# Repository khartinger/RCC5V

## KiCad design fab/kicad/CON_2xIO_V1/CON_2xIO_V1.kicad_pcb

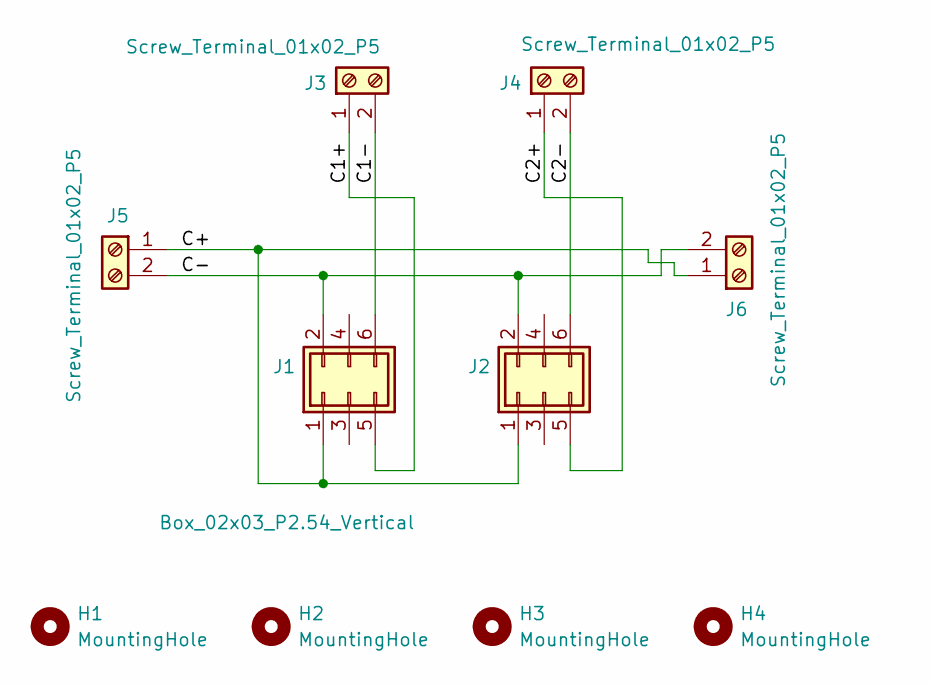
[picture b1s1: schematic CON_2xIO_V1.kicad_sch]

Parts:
H1, H2, H3, H4: MountingHole; MountingHole_2.2mm_M2_Pad_TopBottom_kh
J1: Box_02x03_P2.54_Vertical; Box_02x03_P2.54mm_Vertical_kh
J2: Box_02x03_P2.54mm_Vertical_kh
J3, J4, J5, J6: Screw_Terminal_01x02_P5

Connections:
/C1+: J1.5, J3.1
/C1-: J1.6, J3.2
/C2+: J2.5, J4.1
/C2-: J2.6, J4.2
/C+: J1.1, J2.1, J5.1, J6.1
/C-: J1.2, J2.2, J5.2, J6.2

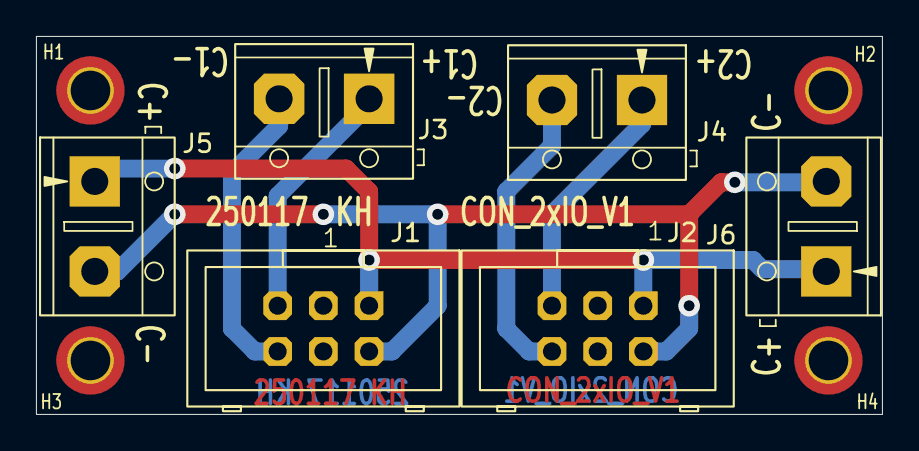
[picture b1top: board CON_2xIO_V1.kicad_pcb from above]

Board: 2 copper layers, 47.0 x 21.0 mm, 10 parts (0 on the bottom side), 6 nets.

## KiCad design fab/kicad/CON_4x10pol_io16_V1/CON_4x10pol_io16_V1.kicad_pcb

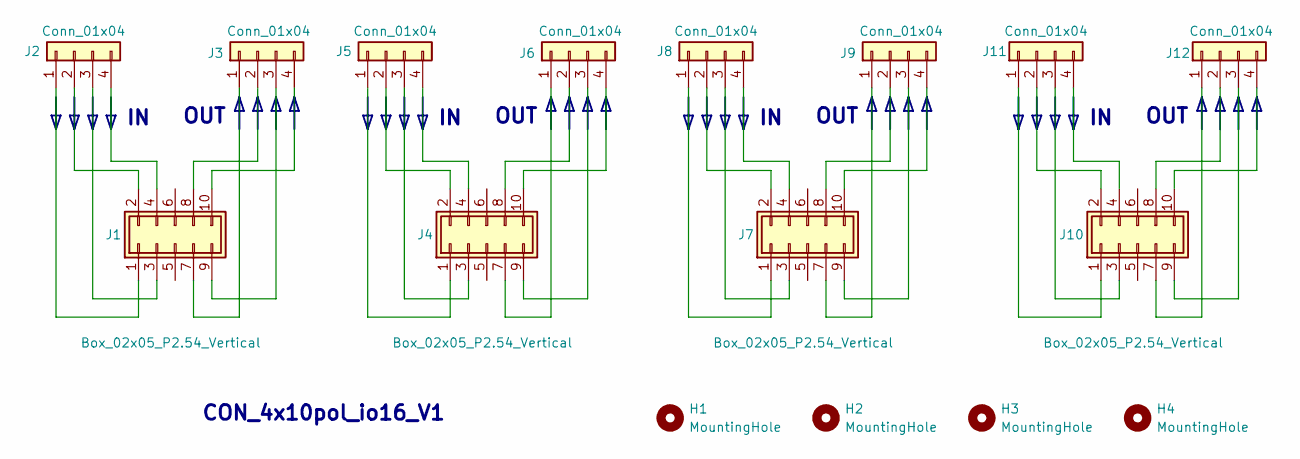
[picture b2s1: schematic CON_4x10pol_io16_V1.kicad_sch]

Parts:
H1, H2, H3, H4: MountingHole; MountingHole_2.2mm_M2_Pad_TopBottom_kh
J1, J4, J7, J10: Box_02x05_P2.54_Vertical; Box_02x05_P2.54mm_Vertical_kh
J2, J3, J5, J6, J8, J9, J11, J12: Conn_01x04; PinSocket_1x04_P2.54mm_8_Vertical_kh

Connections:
unnamed: J1.1, J2.1
unnamed: J1.2, J2.2
unnamed: J1.3, J2.3
unnamed: J1.4, J2.4
unnamed: J1.7, J3.1
unnamed: J1.8, J3.2
unnamed: J1.9, J3.3
unnamed: J1.10, J3.4
unnamed: J4.1, J5.1
unnamed: J4.2, J5.2
unnamed: J4.3, J5.3
unnamed: J4.4, J5.4
unnamed: J4.7, J6.1
unnamed: J4.8, J6.2
unnamed: J4.9, J6.3
unnamed: J4.10, J6.4
unnamed: J7.1, J8.1
unnamed: J7.2, J8.2
unnamed: J7.3, J8.3
unnamed: J7.4, J8.4
unnamed: J7.7, J9.1
unnamed: J7.8, J9.2
unnamed: J7.9, J9.3
unnamed: J7.10, J9.4
unnamed: J10.1, J11.1
unnamed: J10.2, J11.2
unnamed: J10.3, J11.3
unnamed: J10.4, J11.4
unnamed: J10.7, J12.1
unnamed: J10.8, J12.2
unnamed: J10.9, J12.3
unnamed: J10.10, J12.4

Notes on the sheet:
OUT
CON_4x10pol_io16_V1

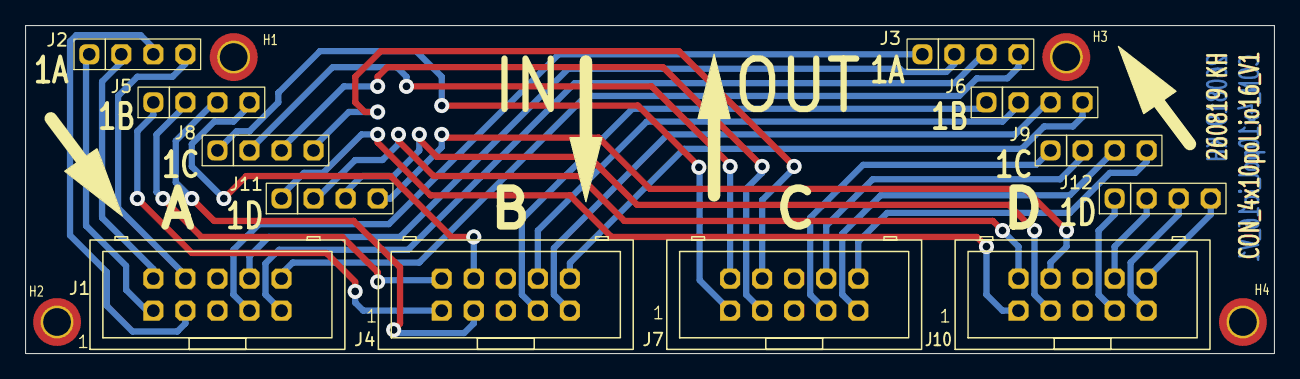
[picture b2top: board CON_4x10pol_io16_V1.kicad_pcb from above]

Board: 2 copper layers, 99.0 x 26.0 mm, 16 parts (0 on the bottom side), 32 nets.

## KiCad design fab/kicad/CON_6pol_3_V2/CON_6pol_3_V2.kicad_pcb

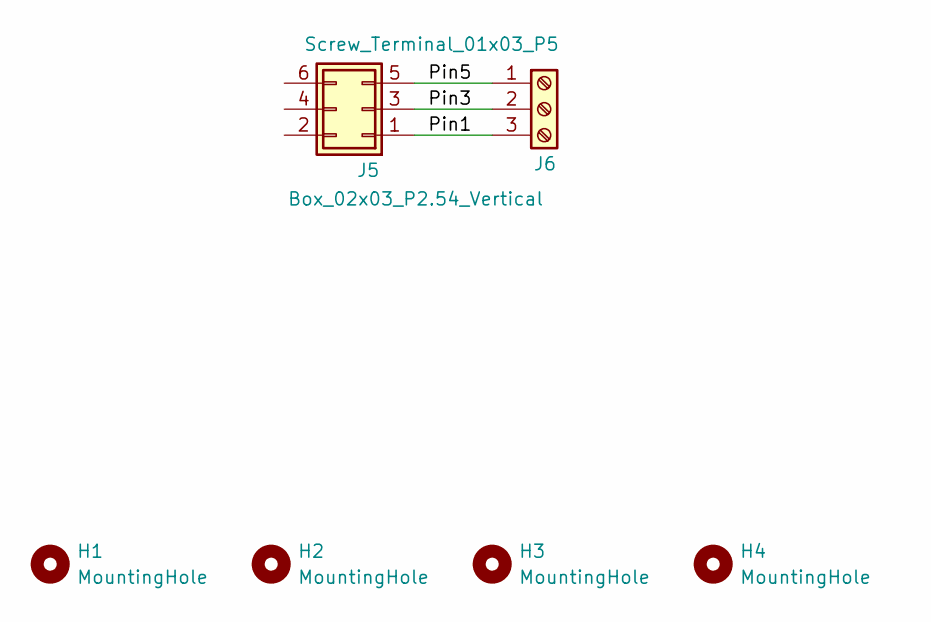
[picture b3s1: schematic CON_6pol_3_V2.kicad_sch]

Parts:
H1, H2, H3, H4: MountingHole; MountingHole_2.2mm_M2_Pad_TopBottom_kh
J5: Box_02x03_P2.54_Vertical; Box_02x03_P2.54mm_Vertical_kh
J6: Screw_Terminal_01x03_P5

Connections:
/Pin1: J5.1, J6.3
/Pin3: J5.3, J6.2
/Pin5: J5.5, J6.1

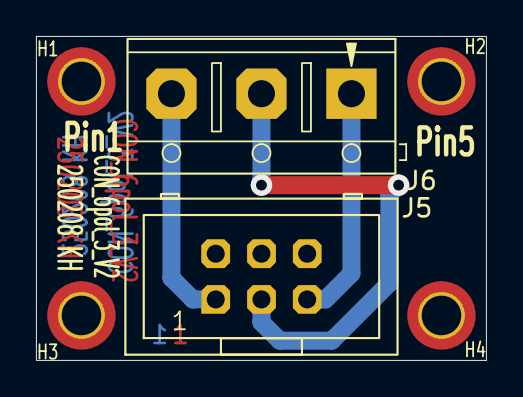
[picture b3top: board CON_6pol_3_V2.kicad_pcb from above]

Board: 2 copper layers, 25.0 x 18.0 mm, 6 parts (0 on the bottom side), 3 nets.

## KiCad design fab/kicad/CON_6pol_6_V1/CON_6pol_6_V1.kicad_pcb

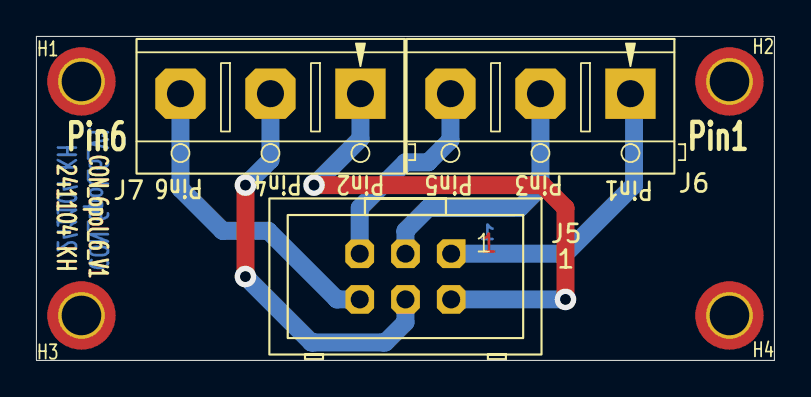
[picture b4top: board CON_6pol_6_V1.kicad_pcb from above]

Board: 2 copper layers, 41.0 x 18.0 mm, 7 parts (0 on the bottom side), 6 nets.

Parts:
H1, H2, H3, H4: MountingHole; MountingHole_2.2mm_M2_Pad_TopBottom_kh
J5: Box_02x03_P2.54_Vertical; Box_02x03_P2.54mm_Vertical_kh
J6, J7: Screw_Terminal_01x03_P5

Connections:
/Pin1: J5.1, J6.1
/Pin2: J5.2, J7.1
/Pin3: J5.3, J6.2
/Pin4: J5.4, J7.2
/Pin5: J5.5, J6.3
/Pin6: J5.6, J7.3

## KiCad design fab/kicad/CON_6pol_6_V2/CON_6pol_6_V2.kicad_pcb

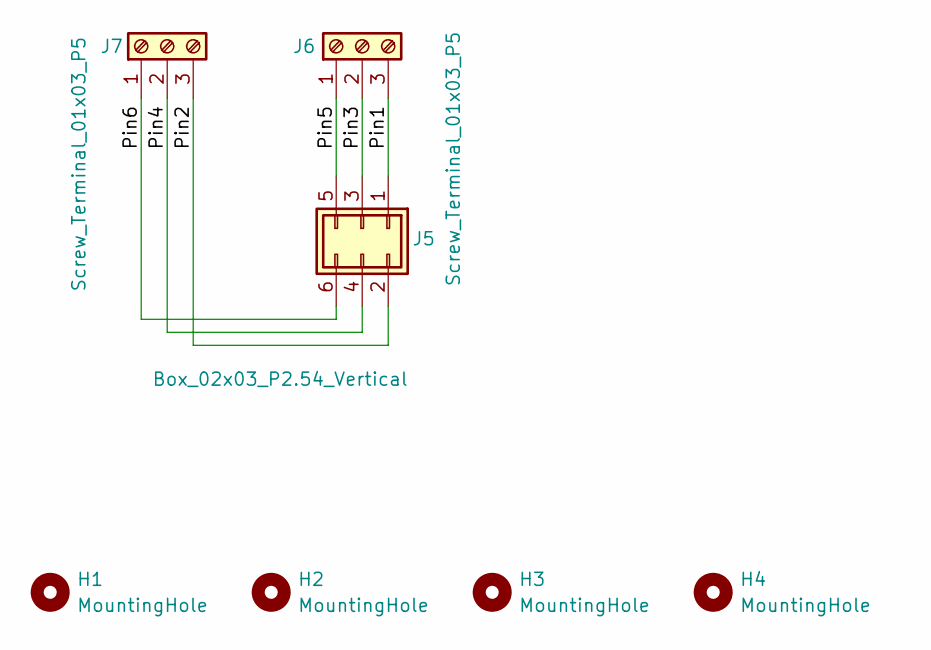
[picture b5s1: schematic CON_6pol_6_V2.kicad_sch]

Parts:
H1, H2, H3, H4: MountingHole; MountingHole_2.2mm_M2_Pad_TopBottom_kh
J5: Box_02x03_P2.54_Vertical; Box_02x03_P2.54mm_Vertical_kh
J6, J7: Screw_Terminal_01x03_P5

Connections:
/Pin1: J5.1, J6.3
/Pin2: J5.2, J7.3
/Pin3: J5.3, J6.2
/Pin4: J5.4, J7.2
/Pin5: J5.5, J6.1
/Pin6: J5.6, J7.1

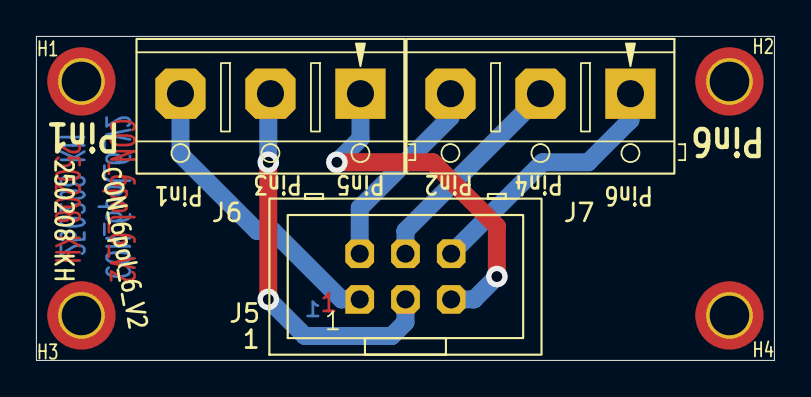
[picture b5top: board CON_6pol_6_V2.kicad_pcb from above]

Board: 2 copper layers, 41.0 x 18.0 mm, 7 parts (0 on the bottom side), 6 nets.

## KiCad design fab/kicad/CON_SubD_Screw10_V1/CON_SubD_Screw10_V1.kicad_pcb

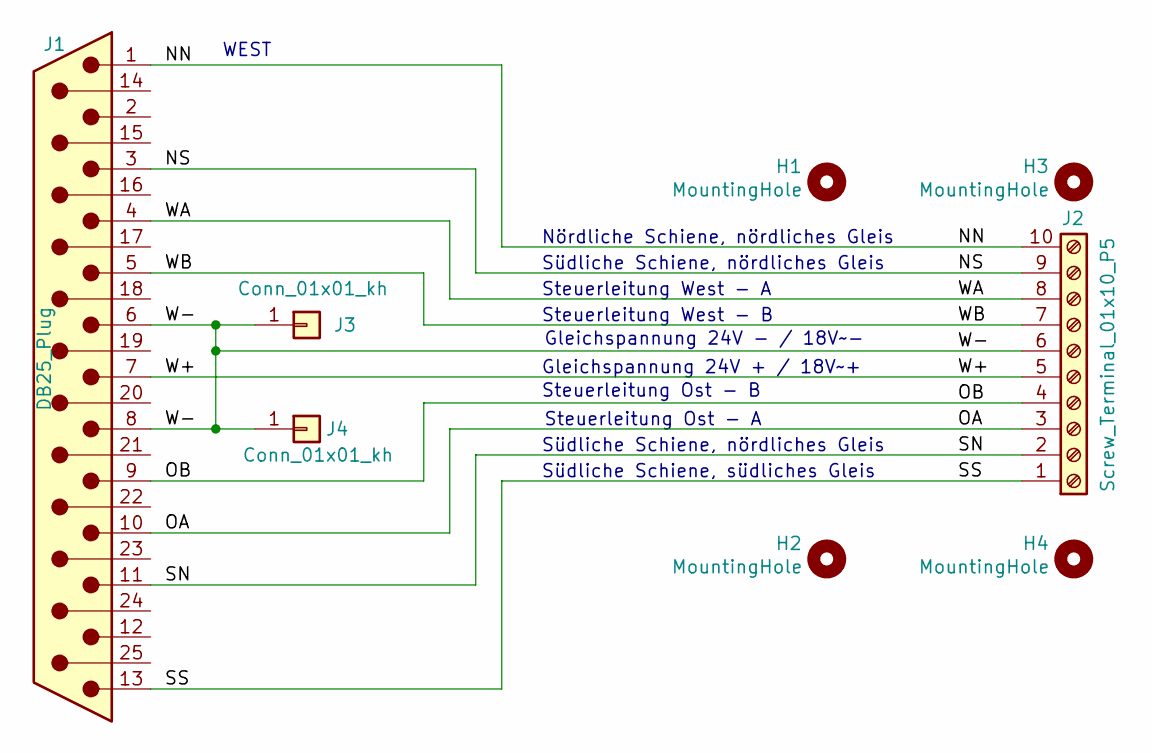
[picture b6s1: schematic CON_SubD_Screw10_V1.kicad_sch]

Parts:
H1, H2, H3, H4: MountingHole; MountingHole_2.7mm_M2.5_DIN965_Pad_TopBottom
J1: DB25_Plug; DSUB-25_Male_Horizontal_P2.77x2.84mm_EdgePinOffset7.70mm_Ho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
J2: Screw_Terminal_01x10_P5
J3, J4: Conn_01x01_kh; Pin_D0.9mm_W1.4mm

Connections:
/NN: J1.1, J2.10
/NS: J1.3, J2.9
/OA: J1.10, J2.3
/OB: J1.9, J2.4
/SN: J1.11, J2.2
/SS: J1.13, J2.1
/W+: J1.7, J2.5
/W-: J1.6, J1.8, J2.6, J3.1, J4.1
/WA: J1.4, J2.8
/WB: J1.5, J2.7

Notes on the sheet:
Südliche Schiene, südliches Gleis
Südliche Schiene, nördliches Gleis
Gleichspannung 24V - / 18V~-
Nördliche Schiene, nördliches Gleis
Steuerleitung West - A
Steuerleitung Ost - B
Steuerleitung West - B
WEST
Gleichspannung 24V + / 18V~+
Steuerleitung Ost - A

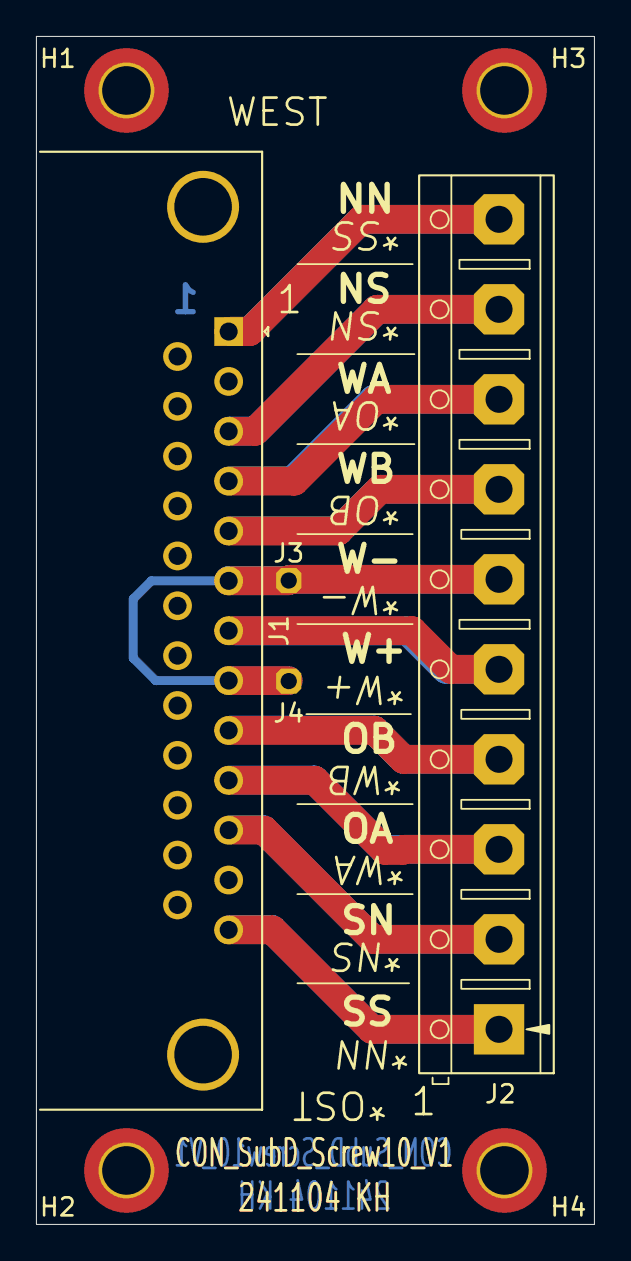
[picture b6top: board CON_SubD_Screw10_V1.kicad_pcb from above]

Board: 2 copper layers, 31.0 x 66.0 mm, 8 parts (0 on the bottom side), 10 nets.
